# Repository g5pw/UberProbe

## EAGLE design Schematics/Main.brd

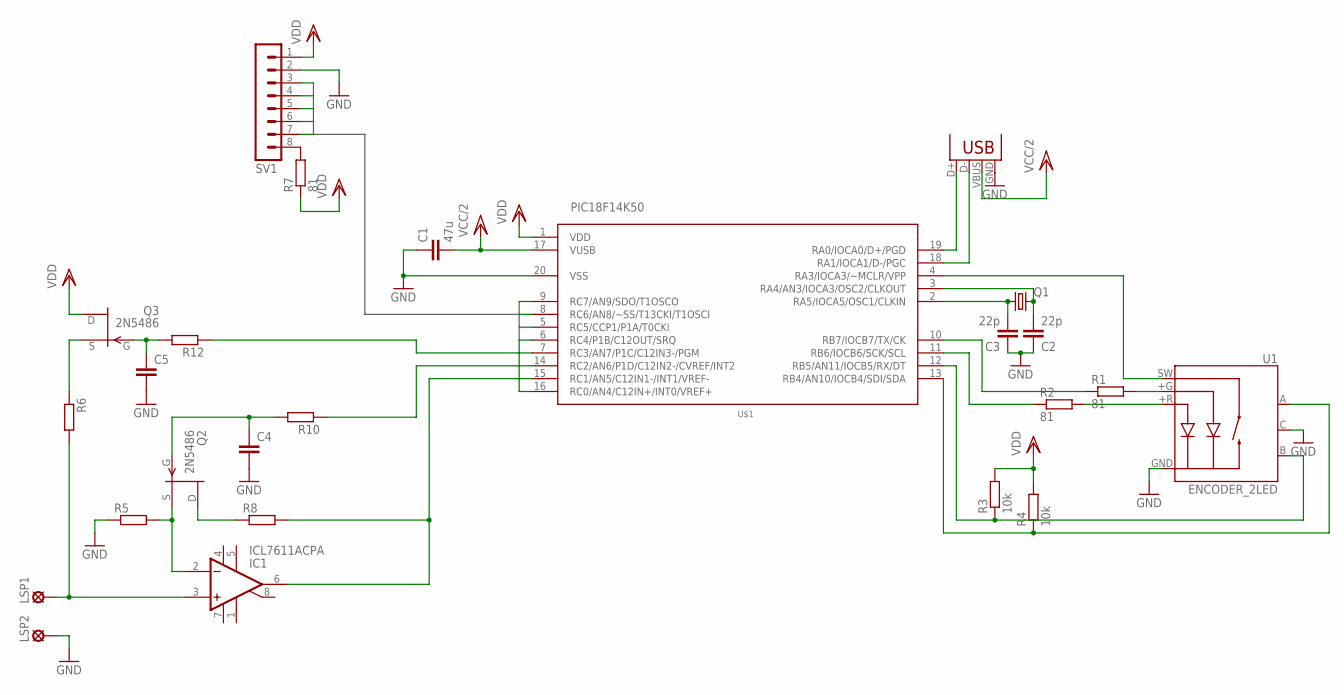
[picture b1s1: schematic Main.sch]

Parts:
C1: 47u; C025-025X050
C2, C3: 22p; C025-025X050
C4, C5: C-EU025-025X050; C025-025X050
IC1: ICL7611ACPA; DIL08
LSP1, LSP2: LSP10
Q1: CRYSTALHC49S; HC49/S
Q2, Q3: 2N5486; TO92-
R1, R2, R7: 81; 0207/7
R3, R4: 10k; 0207/7
R5, R6, R8, R10, R12: R-EU_0207/7; 0207/7
SV1: MA08-1
U1: ENCODER_2LED; ENCODER_LED_2
U$1: PIC18F14K50; DIP20
X1: USBPTH; USB-B-PTH

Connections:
D/~C: SV1.5, U$1.5 (RC5/CCP1/P1A/T0CKI)
GND: C1.1, C2.1, C3.1, C4.2, C5.2, LSP2.MP, R5.1, SV1.2, U1.C, U1.GND (-), U$1.20 (VSS), X1.GND
unnamed: C2.2, Q1.2, U$1.3 (RA4/AN3/IOCA3/OSC2/CLKOUT)
unnamed: U$1.19 (RA0/IOCA0/D+/PGD), X1.D+
unnamed: U$1.18 (RA1/IOCA1/D-/PGC), X1.D-
unnamed: C3.2, Q1.1, U$1.2 (RA5/IOCA5/OSC1/CLKIN)
unnamed: U1.SW, U$1.4 (RA3/IOCA3/~MCLR/VPP)
unnamed: R1.1, U$1.10 (RB7/IOCB7/TX/CK)
unnamed: R1.2, U1.+G
unnamed: Q2.3 (D), R8.1
unnamed: R2.2, U1.+R
unnamed: R2.1, U$1.11 (RB6/IOCB6/SCK/SCL)
unnamed: R3.1, U1.B, U$1.12 (RB5/AN11/IOCB5/RX/DT)
unnamed: R4.1, U1.A, U$1.13 (RB4/AN10/IOCB4/SDI/SDA)
unnamed: IC1.2 (-IN), Q2.2 (S), R5.2
unnamed: IC1.3 (+IN), LSP1.MP, R6.2
unnamed: R7.2, SV1.8
unnamed: IC1.6 (OUT), R8.2, U$1.15 (RC1/AN5/C12IN1-/INT1/VREF-)
unnamed: R10.1, U$1.14 (RC2/AN6/P1D/C12IN2-/CVREF/INT2)
unnamed: R12.1, U$1.7 (RC3/AN7/P1C/C12IN3-/PGM)
unnamed: C4.1, Q2.1 (G), R10.2
unnamed: C5.1, Q3.1 (G), R12.2
unnamed: Q3.2 (S), R6.1
SCLK: SV1.7, U$1.8 (RC6/AN8/~SS/T13CKI/T1OSCI)
SDIN: SV1.6, U$1.9 (RC7/AN9/SDO/T1OSCO)
V+: IC1.7 (V+)
V-: IC1.4 (V-)
VCC/2: C1.2, U$1.17 (VUSB), X1.VBUS
VDD: Q3.3 (D), R3.2, R4.2, R7.1, SV1.1
VUSB: U$1.1 (VDD)
~RES: SV1.4, U$1.16 (RC0/AN4/C12IN+/INT0/VREF+)
~SCE: SV1.3, U$1.6 (RC4/P1B/C12OUT/SRQ)

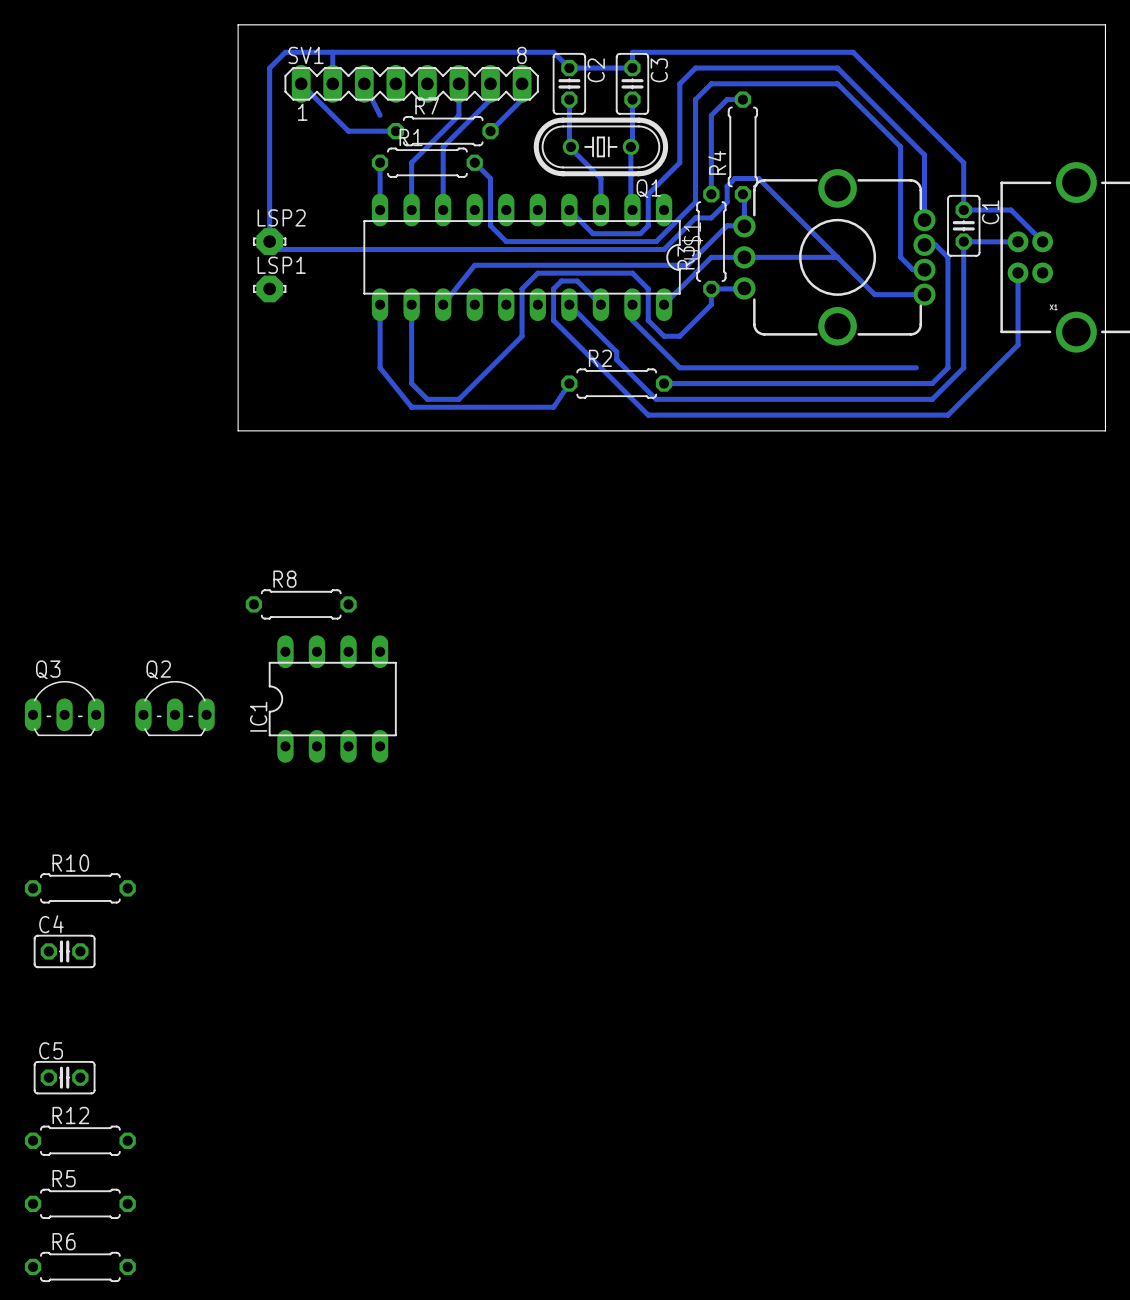
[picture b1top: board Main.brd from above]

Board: 2 copper layers, 69.8 x 32.7 mm, 25 parts (0 on the bottom side), 29 nets.

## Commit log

2011-11-24 Schematic nearly complete
    Too many pins used, will look for alternatives.
2011-11-24 Schematic complete
    Board nearly complete, only one route missing. Will see if 2 resistors are enough to condition the signal.
2011-11-25 Schematics competed
    Updated to use rotary encoder and nokia graphic screen.
2011-12-16 Using VGA and VCR
    Using variable gain amplifier for input and a VCR to inject signals
2011-12-17 Added photo of schematic.
2013-04-04 Add license.

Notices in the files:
parts and their libraries:
SparkFun: Licensing: CC v3.0 Share-Alike You are welcome to use this library for commercial purposes.
